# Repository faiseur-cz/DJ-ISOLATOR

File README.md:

# DJ-ISOLATOR
Open-source project of a 3-band "dj isolator"

When i built my first Pathos rotary mixer, a clone of the infamous Bozak CMA-10-2DL, by australian engineer Miles Stevens-aka Fabric Astronaut-, I knew i needed an isolator... so i bought 3 PCBs, from different horizons... i payed a sh+t lot of money for them... and although they worked well, i thought they were not worth it... dont get me wrong! im not criticizing the products, they are all great and amazing, but i felt i could just make it myself, for less money...
Of course, i ended up paying way more... somehow the price of self satisfaction... I learned a lot - and hopefully you will too!

anyway, lets not loose the point!

I basically copied everything from the very generous ESP (Elliott Sound Products) website.. under project numbers :
- Project 09 : 3-Way Linkwitz Riley Crossover
- Project 153 : Frequency 'Isolator' Equaliser
And a lot of other tips from this great knowledge base.

It is a 24dB/oct filter, with frequencies set up at 310Hz and 3k1Hz. You can change those values up to your tastes, for this I can only advise you to fly on ROD ELLIOTT's WEBSITE!!
You can use high quality potentiometers RK27 or more standard ones (i like center detent in those spots).
Either Molex or IDC 10pins connectors are possible for In/Out and power.

https://sound-au.com
https://sound-au.com/project09.htm
https://sound-au.com/project153.htm

https://fabricastronautblog.wordpress.com/2019/06/27/bozak-cma-10-2dl-pt-1-begining/
https://fabricastronautblog.wordpress.com/2016/07/24/pathos-dj-mixer-pt-1/
https://fabricastronautblog.wordpress.com/2016/05/25/dj-isolator-v1-0/

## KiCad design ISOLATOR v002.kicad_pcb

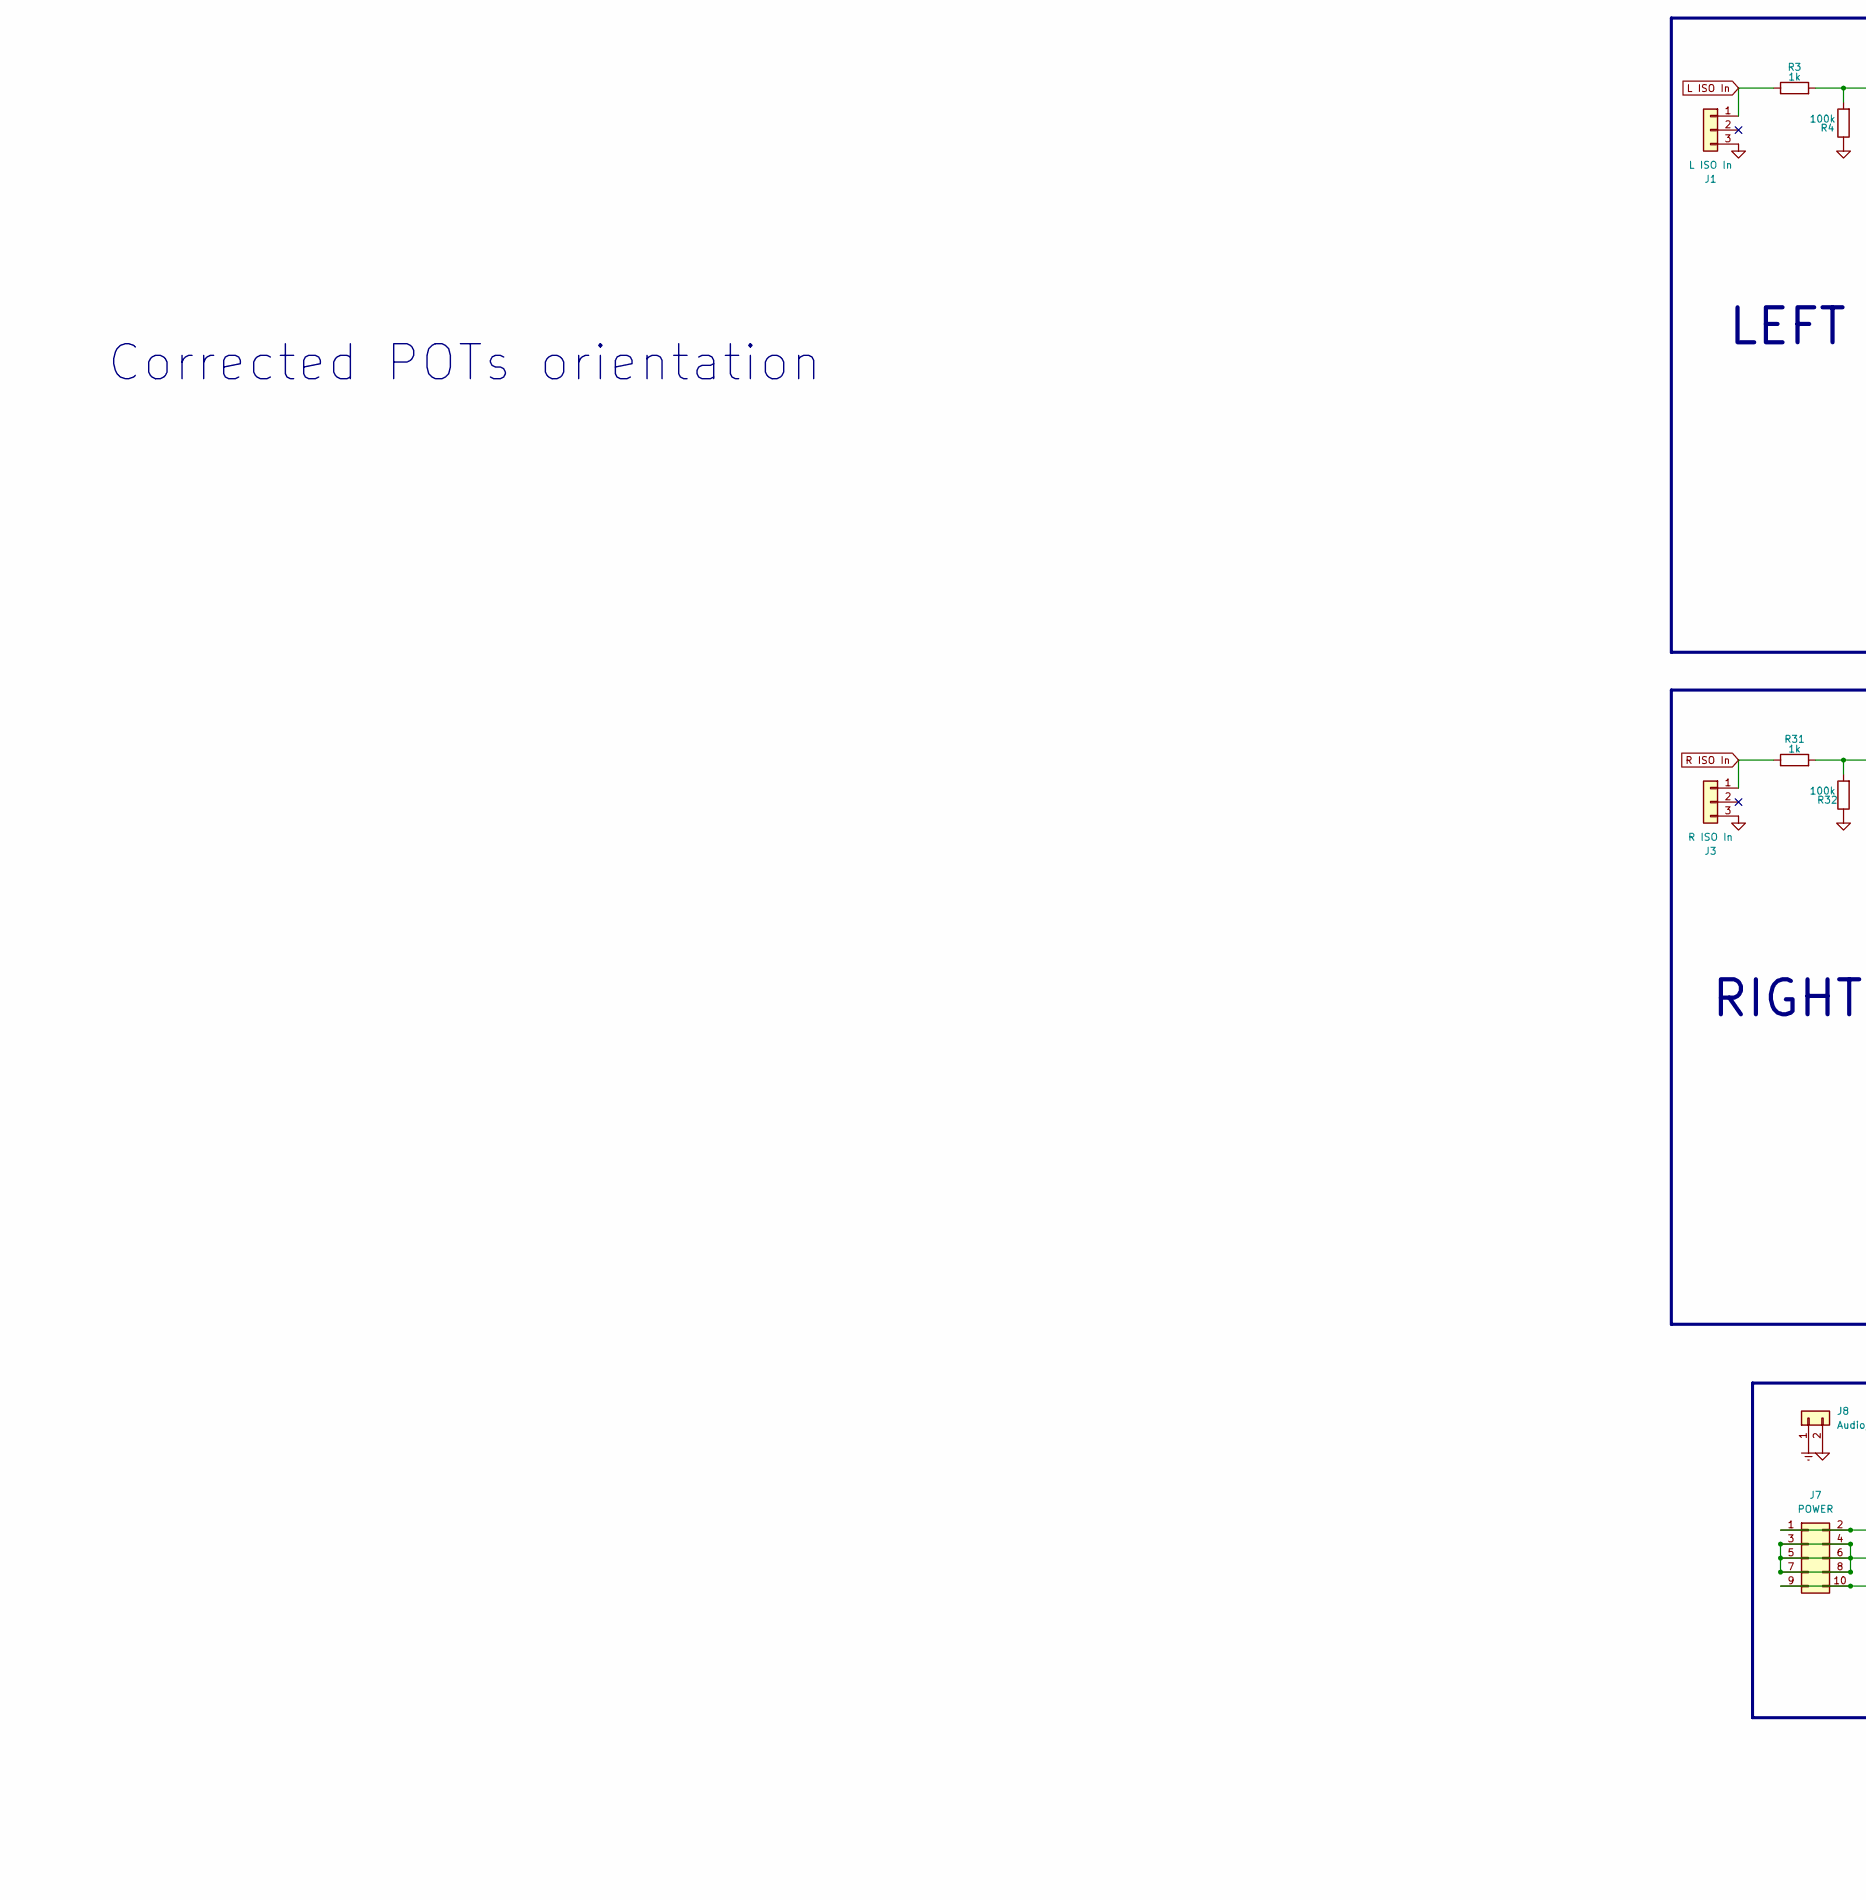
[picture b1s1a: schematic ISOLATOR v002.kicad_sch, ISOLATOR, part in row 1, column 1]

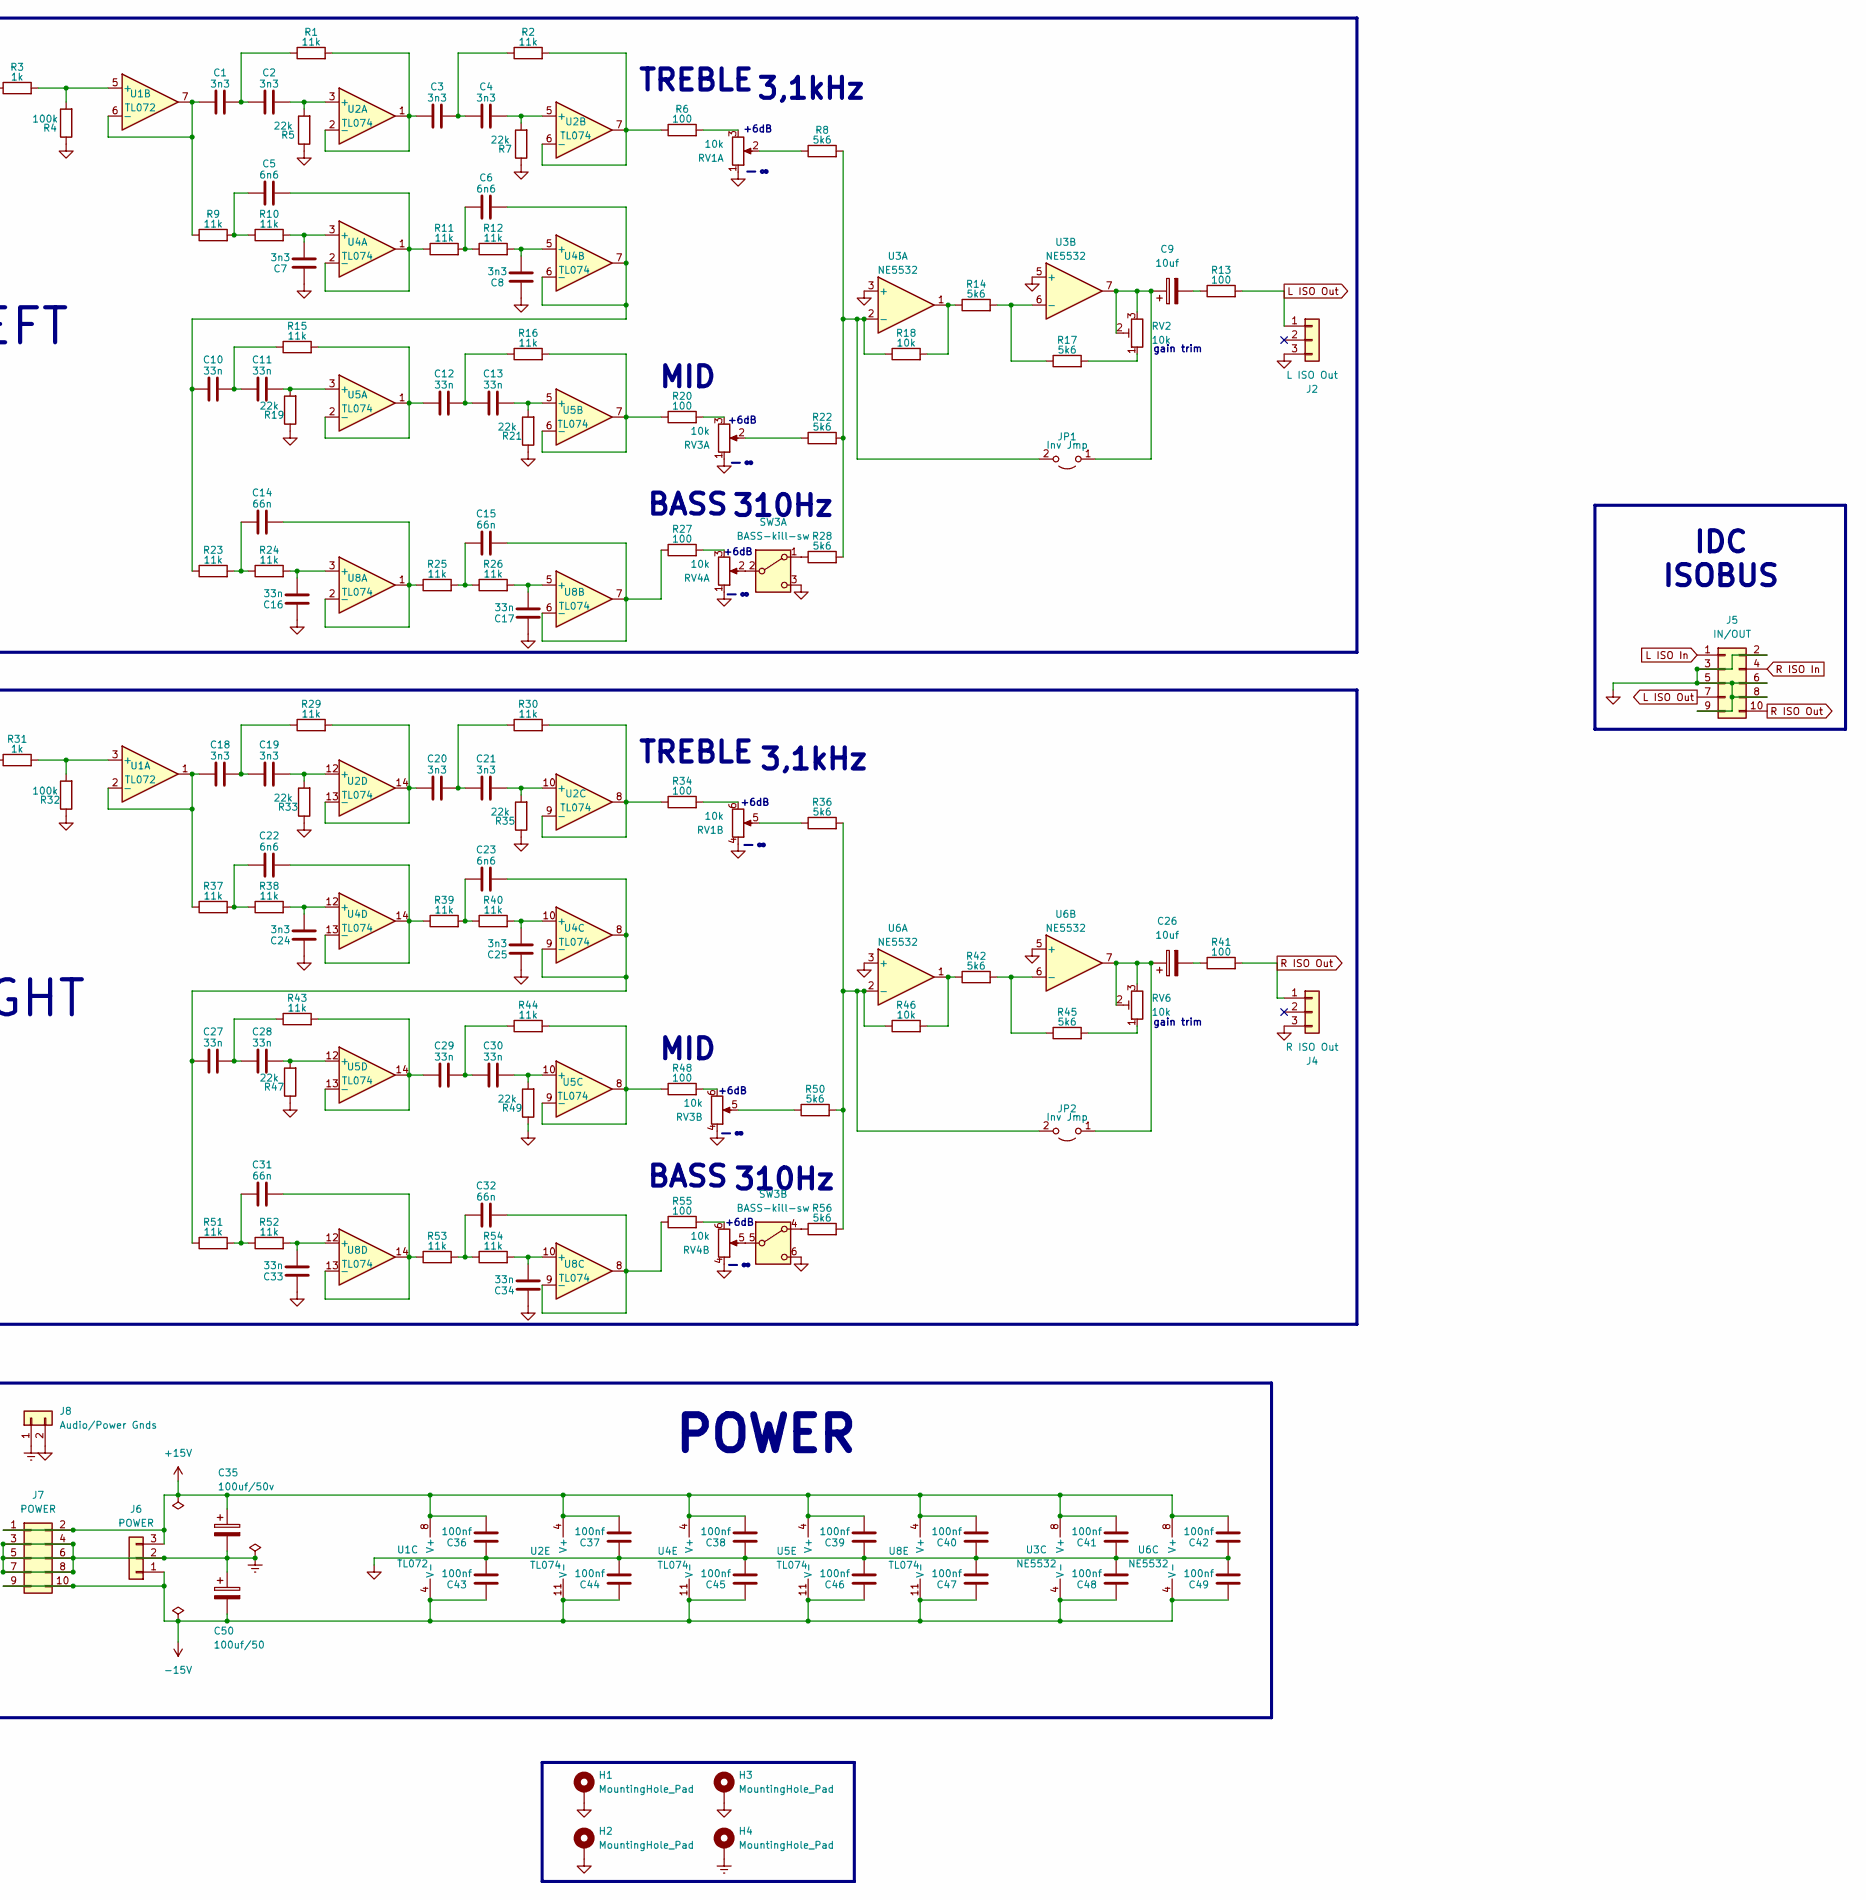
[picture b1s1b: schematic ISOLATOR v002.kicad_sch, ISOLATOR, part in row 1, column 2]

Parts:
C1, C2, C3, C4, C7, C8, C18, C19, C20, C21, C24, C25: 3n3; C_Rect_L7.2mm_W3.5mm_P5.00mm_FKS2_FKP2_MKS2_MKP2
C5, C6, C22, C23: 6n6; C_Rect_L7.2mm_W3.5mm_P5.00mm_FKS2_FKP2_MKS2_MKP2
C9, C26: 10uf; CP_Radial_D8.0mm_P2.50mm
C10, C11, C12, C13, C16, C17, C27, C28, C29, C30, C33, C34: 33n; C_Rect_L7.2mm_W3.5mm_P5.00mm_FKS2_FKP2_MKS2_MKP2
C14, C15, C31, C32: 66n; C_Rect_L7.2mm_W3.5mm_P5.00mm_FKS2_FKP2_MKS2_MKP2
C35: 100uf/50v; CP_Radial_D10.0mm_P2.50mm
C36, C37, C38, C39, C40, C41, C42, C43, C44, C45, C46, C47, C48, C49: 100nf; C_Disc_D5.0mm_W2.5mm_P5.00mm
C50: 100uf/50; CP_Radial_D10.0mm_P2.50mm
H1, H2, H3, H4: MountingHole_Pad; MountingHole_3.2mm_M3_Pad_Via
J1: L ISO In; Molex_KK-254_AE-6410-03A_1x03_P2.54mm_Vertical
J2: L ISO Out; Molex_KK-254_AE-6410-03A_1x03_P2.54mm_Vertical
J3: R ISO In; Molex_KK-254_AE-6410-03A_1x03_P2.54mm_Vertical
J4: R ISO Out; Molex_KK-254_AE-6410-03A_1x03_P2.54mm_Vertical
J5: IN/OUT; IDC-Header_2x05_P2.54mm_Horizontal
J6: POWER; Molex_KK-254_AE-6410-03A_1x03_P2.54mm_Vertical
J7: POWER; IDC-Header_2x05_P2.54mm_Horizontal
J8: Audio/Power Gnds; PinHeader_1x02_P2.54mm_Vertical
JP1, JP2: Inv Jmp; R_Axial_DIN0207_L6.3mm_D2.5mm_P10.16mm_Horizontal
R1, R2, R9, R10, R11, R12, R15, R16, R23, R24, R25, R26, R29, R30, R37, R38, R39, R40, R43, R44, R51, R52, R53, R54: 11k; R_Axial_DIN0207_L6.3mm_D2.5mm_P7.62mm_Horizontal
R3, R31: 1k; R_Axial_DIN0207_L6.3mm_D2.5mm_P7.62mm_Horizontal
R4, R32: 100k; R_Axial_DIN0207_L6.3mm_D2.5mm_P7.62mm_Horizontal
R5, R7, R19, R21, R33, R35, R47, R49: 22k; R_Axial_DIN0207_L6.3mm_D2.5mm_P7.62mm_Horizontal
R6, R13, R20, R27, R34, R41, R48, R55: 100; R_Axial_DIN0207_L6.3mm_D2.5mm_P7.62mm_Horizontal
R8, R14, R17, R22, R28, R36, R42, R45, R50, R56: 5k6; R_Axial_DIN0207_L6.3mm_D2.5mm_P7.62mm_Horizontal
R18, R46: 10k; R_Axial_DIN0207_L6.3mm_D2.5mm_P7.62mm_Horizontal
RV1, RV3, RV4: 10k; RK27 + standard dual pot
RV2, RV6: 10k; Potentiometer_Piher_PT-6-H_Horizontal
SW3: BASS-kill-sw; 100DP1T1B4M7QE
U1: TL072; DIP-8_W7.62mm_Socket
U2, U4, U5, U8: TL074; DIP-14_W7.62mm_Socket
U3, U6: NE5532; DIP-8_W7.62mm_Socket

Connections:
+15V: C35.1, C36.2, C37.2, C38.2, C39.2, C40.2, C41.2, C42.2, J6.3, J7.1, J7.2, U1.8 (V+), U2.4 (V+), U3.8 (V+), U4.4 (V+), U5.4 (V+), U6.8 (V+), U8.4 (V+)
-15V: C43.1, C44.1, C45.1, C46.1, C47.1, C48.1, C49.1, C50.2, J6.1, J7.9, J7.10, U1.4 (V-), U2.11 (V-), U3.4 (V-), U4.11 (V-), U5.11 (V-), U6.4 (V-), U8.11 (V-)
GND: C7.1, C8.1, C16.1, C17.1, C24.1, C25.1, C33.1, C34.1, C36.1, C37.1, C38.1, C39.1, C40.1, C41.1, C42.1, C43.2, C44.2, C45.2, C46.2, C47.2, C48.2, C49.2, H1.1, H2.1, H3.1, J1.3, J2.3, J3.3, J4.3, J5.2, J5.3, J5.5, J5.6, J5.8, J5.9, J8.2, R4.1, R5.1, R7.1, R19.1, R21.1, R32.1, R33.1, R35.1, R47.1, R49.1, RV1.1, RV1.4, RV3.1, RV3.4, RV4.1, RV4.4, SW3.3 (C), SW3.6 (C), U3.3 (+), U3.5 (+), U6.3 (+), U6.5 (+)
GNDREF: C35.2, C50.1, H4.1, J6.2, J7.3, J7.4, J7.5, J7.6, J7.7, J7.8, J8.1
L ISO In: J1.1, J5.1, R3.1
L ISO Out: J2.1, J5.7, R13.2
unnamed: C1.2, C2.1, R1.1
unnamed: C3.2, C4.1, R2.1
unnamed: C5.1, R9.2, R10.1
unnamed: C6.1, R11.2, R12.1
unnamed: C9.2, R13.1
unnamed: C10.2, C11.1, R15.1
unnamed: C12.2, C13.1, R16.1
unnamed: C14.1, R23.2, R24.1
unnamed: C15.1, R25.2, R26.1
unnamed: C18.2, C19.1, R29.1
unnamed: C20.2, C21.1, R30.1
unnamed: C22.1, R37.2, R38.1
unnamed: C23.1, R39.2, R40.1
unnamed: C26.2, R41.1
unnamed: C27.2, C28.1, R43.1
unnamed: C29.2, C30.1, R44.1
unnamed: C31.1, R51.2, R52.1
unnamed: C32.1, R53.2, R54.1
unnamed: C9.1, JP1.1 (A), RV2.2, RV2.3, U3.7
unnamed: JP1.2 (B), R8.2, R18.1, R22.2, R28.2, U3.2 (-)
unnamed: C26.1, JP2.1 (A), RV6.2, RV6.3, U6.7
unnamed: JP2.2 (B), R36.2, R46.1, R50.2, R56.2, U6.2 (-)
unnamed: R6.2, RV1.3
unnamed: R8.1, RV1.2
unnamed: R14.1, R18.2, U3.1
unnamed: R17.2, RV2.1
unnamed: R20.2, RV3.3
unnamed: R22.1, RV3.2
unnamed: R27.2, RV4.3
unnamed: R34.2, RV1.6
unnamed: R36.1, RV1.5
unnamed: R42.1, R46.2, U6.1
unnamed: R45.2, RV6.1
unnamed: R48.2, RV3.6
unnamed: R50.1, RV3.5
unnamed: R55.2, RV4.6
unnamed: R28.1, SW3.1 (A)
unnamed: RV4.2, SW3.2 (B)
unnamed: R56.1, SW3.4 (A)
unnamed: RV4.5, SW3.5 (B)
unnamed: R31.2, R32.2, U1.3 (+)
unnamed: C18.1, R37.1, U1.1, U1.2 (-)
unnamed: R3.2, R4.2, U1.5 (+)
unnamed: C1.1, R9.1, U1.6 (-), U1.7
unnamed: C2.2, R5.2, U2.3 (+)
unnamed: C3.1, R1.2, U2.1, U2.2 (-)
unnamed: C4.2, R7.2, U2.5 (+)
unnamed: R2.2, R6.1, U2.6 (-), U2.7
unnamed: C21.2, R35.2, U2.10 (+)
unnamed: R30.2, R34.1, U2.8, U2.9 (-)
unnamed: C19.2, R33.2, U2.12 (+)
unnamed: C20.1, R29.2, U2.13 (-), U2.14
unnamed: R14.2, R17.1, U3.6 (-)
unnamed: C7.2, R10.2, U4.3 (+)
unnamed: C5.2, R11.1, U4.1, U4.2 (-)
unnamed: C8.2, R12.2, U4.5 (+)
unnamed: C6.2, C10.1, R23.1, U4.6 (-), U4.7
unnamed: C25.2, R40.2, U4.10 (+)
unnamed: C23.2, C27.1, R51.1, U4.8, U4.9 (-)
unnamed: C24.2, R38.2, U4.12 (+)
unnamed: C22.2, R39.1, U4.13 (-), U4.14
unnamed: C11.2, R19.2, U5.3 (+)
unnamed: C12.1, R15.2, U5.1, U5.2 (-)
unnamed: C13.2, R21.2, U5.5 (+)
unnamed: R16.2, R20.1, U5.6 (-), U5.7
unnamed: C30.2, R49.2, U5.10 (+)
unnamed: R44.2, R48.1, U5.8, U5.9 (-)
unnamed: C28.2, R47.2, U5.12 (+)
unnamed: C29.1, R43.2, U5.13 (-), U5.14
unnamed: R42.2, R45.1, U6.6 (-)
unnamed: C16.2, R24.2, U8.3 (+)
unnamed: C14.2, R25.1, U8.1, U8.2 (-)
unnamed: C17.2, R26.2, U8.5 (+)
unnamed: C15.2, R27.1, U8.6 (-), U8.7
unnamed: C34.2, R54.2, U8.10 (+)
unnamed: C32.2, R55.1, U8.8, U8.9 (-)
unnamed: C33.2, R52.2, U8.12 (+)
unnamed: C31.2, R53.1, U8.13 (-), U8.14
R ISO In: J3.1, J5.4, R31.1
R ISO Out: J4.1, J5.10, R41.2

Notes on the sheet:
BASS
LEFT
+6dB
gain trim
MID
TREBLE
IDC ISOBUS
310Hz
RIGHT
Corrected POTs orientation
3,1kHz
POWER

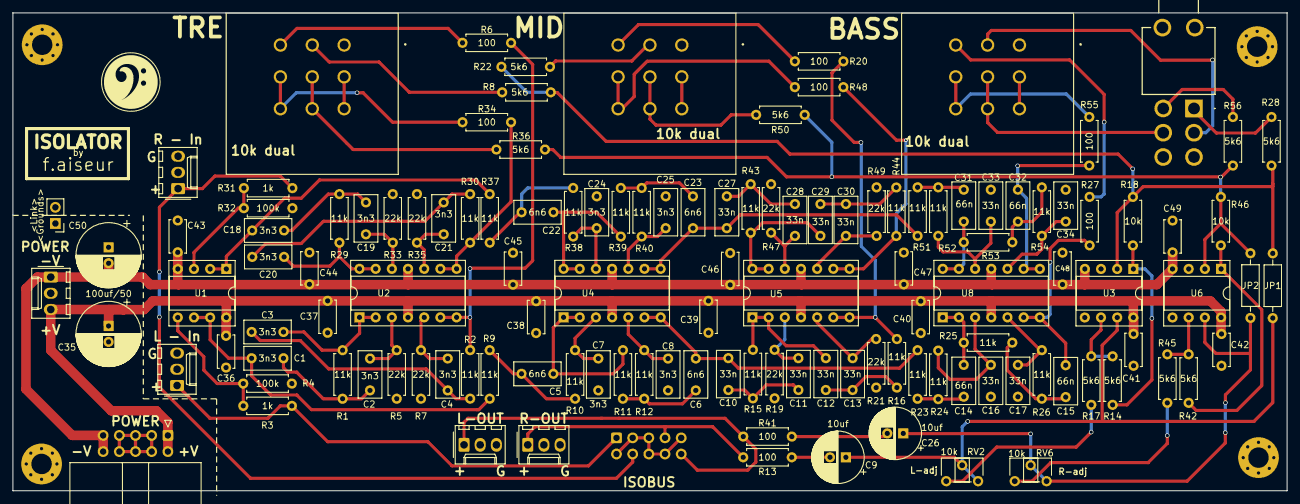
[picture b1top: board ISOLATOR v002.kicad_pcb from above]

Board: 2 copper layers, 200.0 x 75.0 mm, 133 parts (1 on the bottom side), 86 nets.

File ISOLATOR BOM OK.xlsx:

Qty | Designator | Value | Footprint | LINK | Price (total)
CAPACITORS
Film
4 | C15,C32,C14,C31 | 66n (68n) | L7.2mm_W3.5mm_P5.00mm_FKS2_FKP2_MKS2_MKP2 | https://www.mouser.fr/ProductDetail/Panasonic/ECQ-E2683JB?qs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 | 1.64 | https://www.mouser.fr/ProductDetail/505-MKS2.068-50-10 | 2.05 €
12 | C16,C12,C17,C29,C34,C10,C11,C33,C13,C30,C27,C28 | 33n | L7.2mm_W3.5mm_P5.00mm_FKS2_FKP2_MKS2_MKP2 | https://www.mouser.fr/ProductDetail/WIMA/MKS4D023302A00KSSD?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 | 3.34
4 | C23,C22,C5,C6 | 6n6 (6n8) | L7.2mm_W3.5mm_P5.00mm_FKS2_FKP2_MKS2_MKP2 | https://www.mouser.fr/ProductDetail/505-MKP2J016801C00KS | 2.38
12 | C8,C20,C19,C25,C7,C2,C1,C24,C21,C18,C4,C3 | 3n3 | L7.2mm_W3.5mm_P5.00mm_FKS2_FKP2_MKS2_MKP2 | https://www.mouser.fr/ProductDetail/WIMA/FKS2D013301A00KSSD?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 | 3.9
Electro
2 | C9,C26 | 10uf | CP_Radial_D8.0mm_P2.50mm | https://www.mouser.fr/ProductDetail/KYOCERA-AVX/REF0612100M1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 | 0.52
2 | C35, C50 | 100uf/50v | CP_Radial_D10.0mm_P2.50mm | https://www.mouser.fr/ProductDetail/Rubycon/50TXW100MEFC6.3X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 | 2.02
Ceramic
14 | C42,C36,C43,C39,C45,C41,C48,C40,C44,C47,C49, C37,C38,C46 | 100nf | C_Disc_D5.0mm_W2.5mm_P5.00mm | https://www.mouser.fr/ProductDetail/TDK/FK26C0G1H104J?qs=zLB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 | 4.33
CONNECTORS
5 | J1, J2, J3, J4, J6 | L ISO In, R ISO In, … | Molex_KK-254_AE-6410-03A_1x03_P2.54mm_Vertical | https://www.gmelectronic.com/v/1497520/kk254-3pinm-plug-conn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 | 0.25 | 800-095
1 | J5, J7 | IN/OUT, POWER | IDC-Header_2x05_P2.54mm_Horizontal | https://www.gmelectronic.com/v/1498388/kls-mlw10g-plug-conne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 | 0.42 | 800-035
JUMPERS
1 | J8 | Aud/Pwr Gnds | PinHeader_1x02_P2.54mm_Vertical | Resistor leg or 0ohm resistor |  | you can insulate them, it doesn’t hurt..
2 | JP1,JP2 | Inv Jmp | R_Axial_DIN0207_L6.3mm_D2.5mm_P10.16mm_Horizontal | Resistor leg or 0ohm resistor |  | you can insulate them, it doesn’t hurt..
RESISTORS
8 | R13,R48,R41,R6,R27,R34, R55,R20 | 100 | DIN0207_L6.3mm_D2.5mm_P7.62mm_Horizontal
10 | R17,R45,R42,R8,R14,R22, R56,R50,R36,R28 | 5k6 | DIN0207_L6.3mm_D2.5mm_P7.62mm_Horizontal
8 | R21,R33,R5,R19,R49,R47, R7,R35 | 22k | DIN0207_L6.3mm_D2.5mm_P7.62mm_Horizontal
2 | R31,R3 | 1k | DIN0207_L6.3mm_D2.5mm_P7.62mm_Horizontal
2 | R4,R32 | 100k | DIN0207_L6.3mm_D2.5mm_P7.62mm_Horizontal
24 | R40,R24,R11,R2,R53,R9, R52,R39,R10,R23,R30,R54,R38,R29,R51,R12,R37, R15,R1,R25,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 | 11k | R_Axial_DIN0207_L6.3mm_D2.5mm_P7.62mm_Horizontal
2 | R46,R18 | 10k | R_Axial_DIN0207_L6.3mm_D2.5mm_P7.62mm_Horizontal
TRIMMERS / POTENTIOMETERS
2 | RV2,RV6 | 10k | Potentiometer_Piher_PT-6-H_Horizontal | https://www.gmelectronic.com/v/1486444/piher-pt6hk010-carbon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 | 0.96 | 112-177
3 | RV3,RV1,RV4 | 10k | RK27 // OR // standard dual pot |  | 30 | Ebay,Mouser….
Toggle SWITCH
1 | SW3 | BASS-kill-sw | 100DP1T1B4M7QE | https://www.mouser.fr/ProductDetail/E-Switch/100DP1T1B4M7QE?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 | 4.58
ICs
1 | U1 | TL072 | DIP-8_W7.62mm_Socket | https://www.gmelectronic.com/v/1490183/texas-instruments-tl072cp | 0.76 | 311-013
4 | U5,U2,U8,U4 | TL074 | DIP-14_W7.62mm_Socket | https://www.gmelectronic.com/v/1487648/texas-instruments-tl074cn | 2.87 | 311-014
2 | U6,U3 | NE5532 | DIP-8_W7.62mm_Socket | https://www.gmelectronic.com/v/1490181/texas-instruments-ne5532p | 1.16 | https://www.gmelectronic.com/v/1490181/texas-instruments-ne5532p | 1.12 €
TOTAL COST |  |  |  |  | 59.13 | IF RK27
